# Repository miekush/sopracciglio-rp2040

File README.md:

# Sopracciglio RP2040
Raspberry Pi RP2040 based Sopracciglio Board for use with 2026 Open Sauce Badge

# Schematic

# Layout

# Installation

1. Clone repo to a folder of your choice
2. Open the project in KiCad V10.99
3. "Save As" with the name of your project
4. Enjoy! :)

# License

miekush supports the open source hardware community by sharing hardware design files freely on GitHub!

Designed by Mike Kushnerik (miekush)

Licensed under [Creative Commons Attribution-ShareAlike CC BY-SA 4.0](http://creativecommons.org/licenses/by-sa/4.0/)

All text above must be included in any redistribution!

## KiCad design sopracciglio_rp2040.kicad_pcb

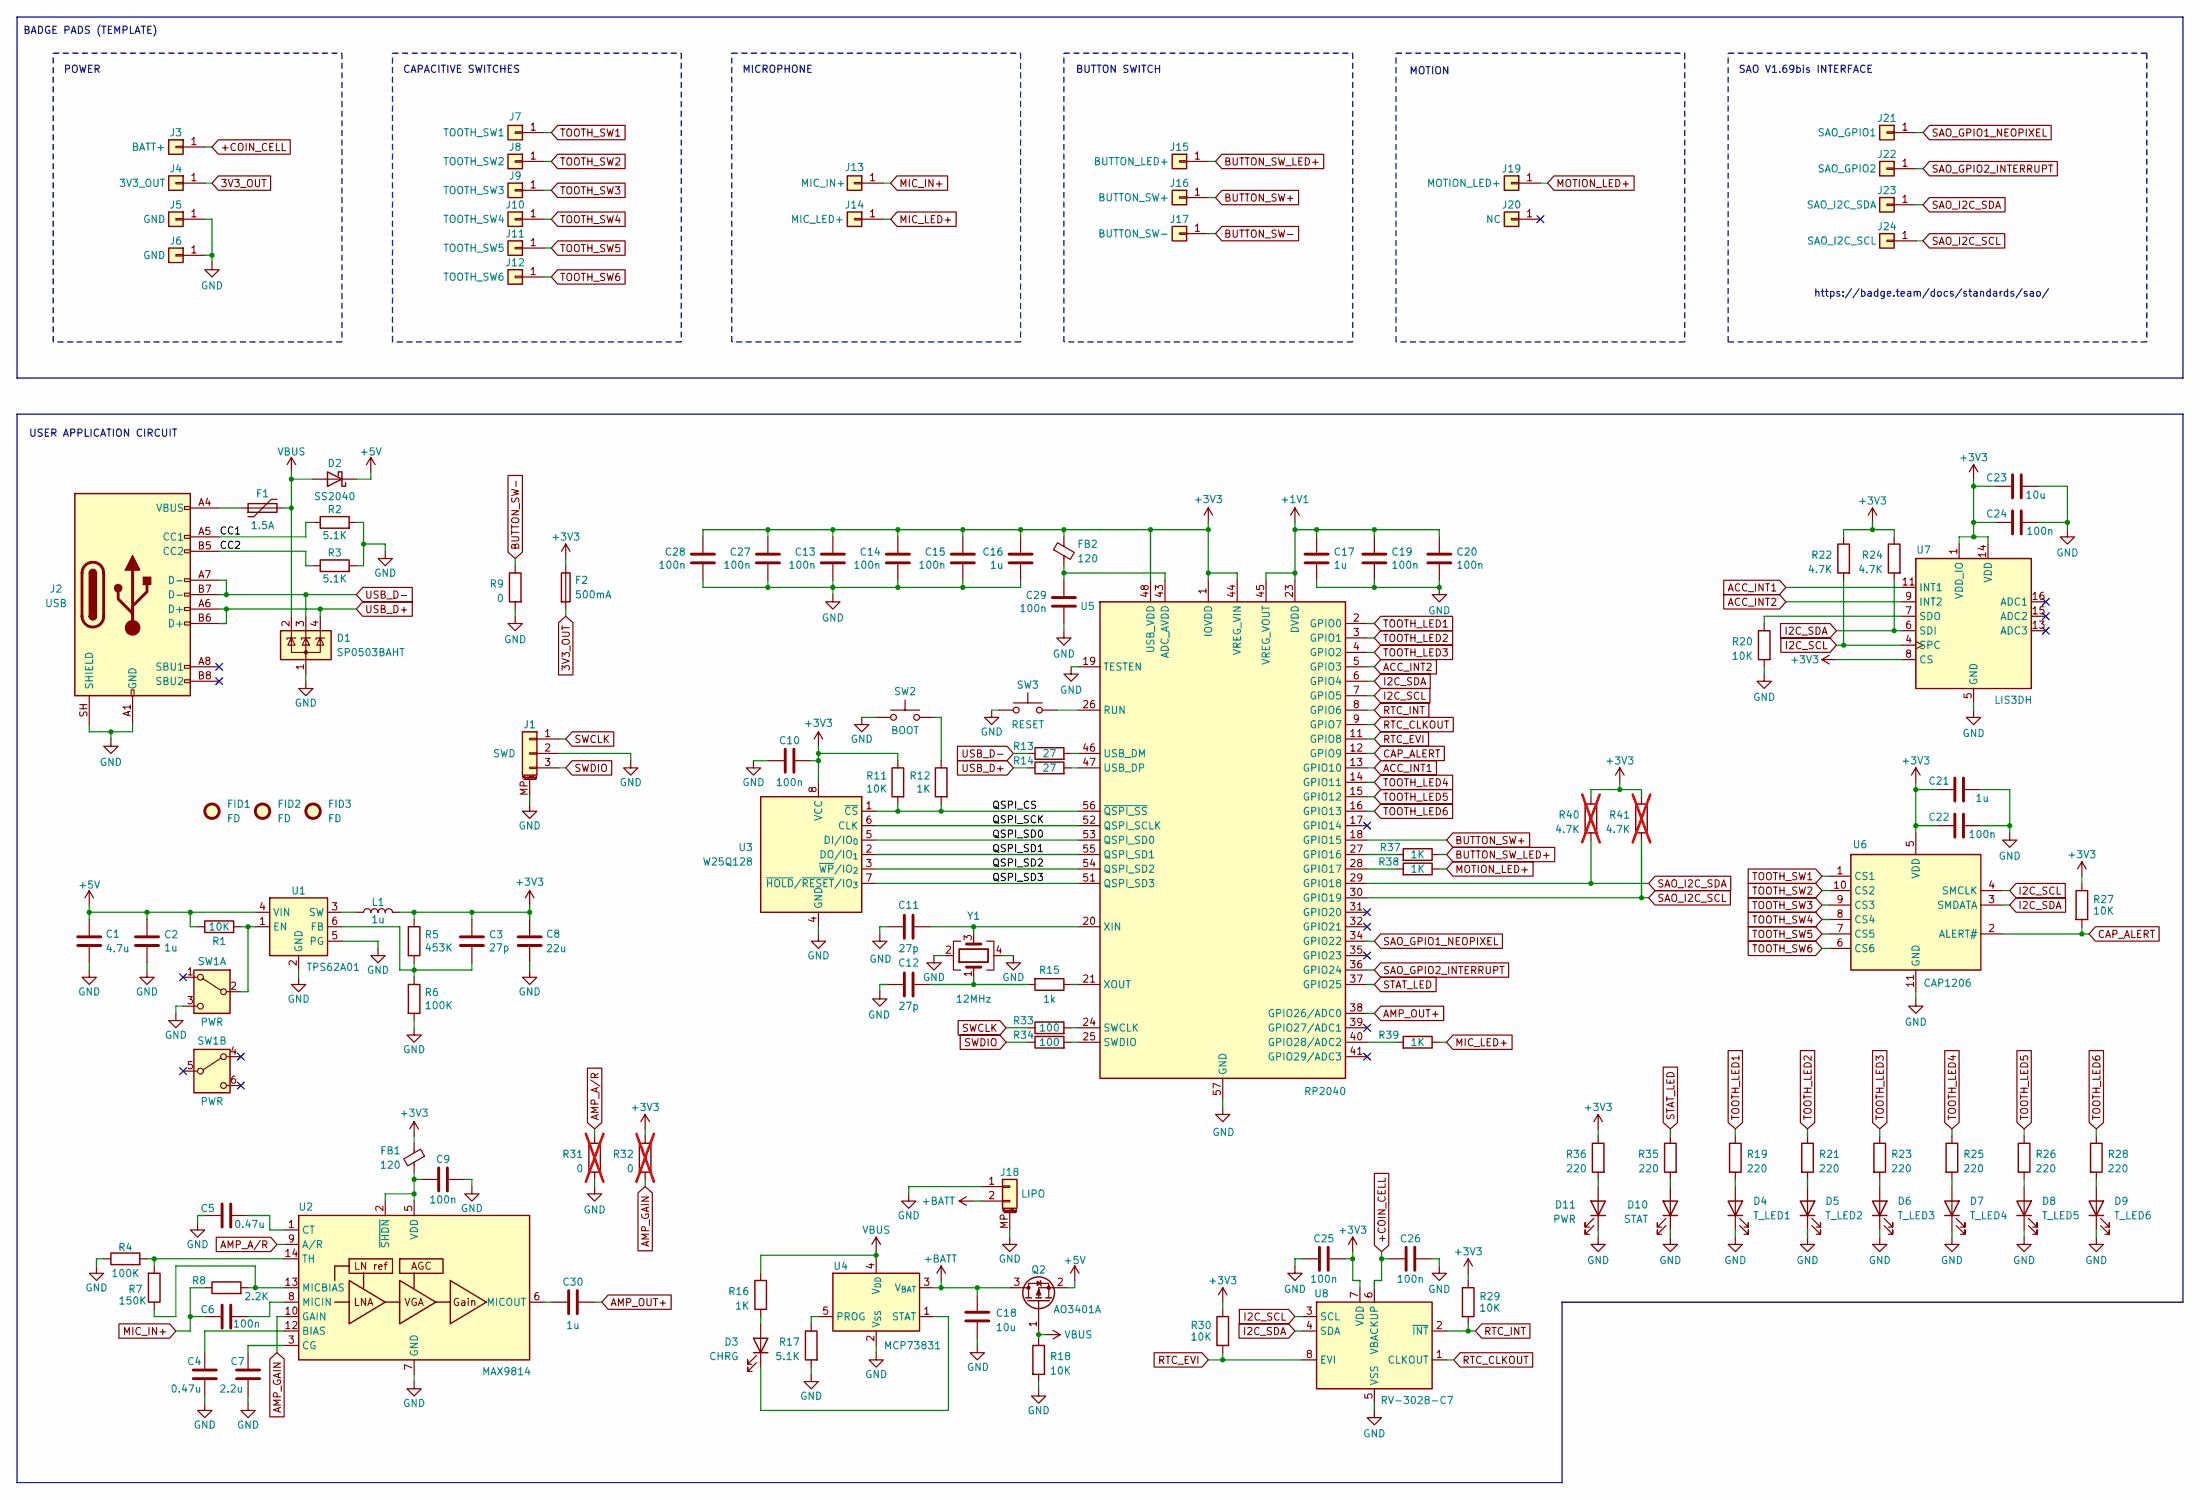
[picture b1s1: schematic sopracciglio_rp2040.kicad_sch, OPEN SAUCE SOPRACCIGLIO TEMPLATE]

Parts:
C1: 4.7u; C_0805_2012Metric
C2, C16, C17, C21, C30: 1u; C_0603_1608Metric
C3, C11, C12: 27p; C_0402_1005Metric
C4, C5: 0.47u; C_0603_1608Metric
C6, C9, C10, C13, C14, C15, C19, C20, C22, C24, C25, C26, C27, C28, C29: 100n; C_0402_1005Metric
C7: 2.2u; C_0603_1608Metric
C8: 22u; C_0805_2012Metric
C18, C23: 10u; C_0805_2012Metric
D1: SP0503BAHT; SOT-143
D2: SS2040; D_SOD-123F
D3: CHRG; LED_0603_1608Metric
D4: T_LED1; LED_0603_1608Metric
D5: T_LED2; LED_0603_1608Metric
D6: T_LED3; LED_0603_1608Metric
D7: T_LED4; LED_0603_1608Metric
D8: T_LED5; LED_0603_1608Metric
D9: T_LED6; LED_0603_1608Metric
D10: STAT; LED_0603_1608Metric
D11: PWR; LED_0603_1608Metric
F1: 1.5A; Fuse_1206_3216Metric
F2: 500mA; Fuse_0402_1005Metric
FB1, FB2: 120; L_0402_1005Metric
FID1, FID2, FID3: FD; Fiducial_0.75mm_Mask1.5mm
J1: SWD; JST_SH_SM03B-SRSS-TB_1x03-1MP_P1.00mm_Horizontal
J2: USB; USB_C_Receptacle_GCT_USB4110
J3: BATT+; castellated_pad
J4: 3V3_OUT; castellated_pad
J5, J6: GND; castellated_pad
J7: TOOTH_SW1; castellated_pad
J8: TOOTH_SW2; castellated_pad
J9: TOOTH_SW3; castellated_pad
J10: TOOTH_SW4; castellated_pad
J11: TOOTH_SW5; castellated_pad
J12: TOOTH_SW6; castellated_pad
J13: MIC_IN+; castellated_pad
J14: MIC_LED+; castellated_pad
J15: BUTTON_LED+; castellated_pad
J16: BUTTON_SW+; castellated_pad
J17: BUTTON_SW-; castellated_pad
J18: LIPO; JST_PH_S2B-PH-SM4-TB_1x02-1MP_P2.00mm_Horizontal
J19: MOTION_LED+; castellated_pad
J20: NC; castellated_pad
J21: SAO_GPIO1; castellated_pad
J22: SAO_GPIO2; castellated_pad
J23: SAO_I2C_SDA; castellated_pad
J24: SAO_I2C_SCL; castellated_pad
L1: 1u; L_1008_2520Metric
Q2: AO3401A; SOT-23
R1, R11, R18, R20, R27, R29, R30: 10K; R_0402_1005Metric
R2, R3, R17: 5.1K; R_0402_1005Metric
R4, R6: 100K; R_0402_1005Metric
R5: 453K; R_0402_1005Metric
R7: 150K; R_0402_1005Metric
R8: 2.2K; R_0402_1005Metric
R9: 0; R_0402_1005Metric
R12, R16, R37, R38, R39: 1K; R_0402_1005Metric
R13, R14: 27; R_0402_1005Metric
R15: 1k; R_0402_1005Metric
R19, R21, R23, R25, R26, R28, R35, R36: 220; R_0402_1005Metric
R22, R24: 4.7K; R_0402_1005Metric
R31, R32: 0; R_0402_1005Metric; not fitted
R33, R34: 100; R_0402_1005Metric
R40, R41: 4.7K; R_0402_1005Metric; not fitted
SW1: PWR; SW_DPDT_CK_JS202011JCQN
SW2: BOOT; SW_Push_1P1T_NO_CK_KMR2
SW3: RESET; SW_Push_1P1T_NO_CK_KMR2
U1: TPS62A01; SOT-23-6
U2: MAX9814; DFN-14-1EP_3x3mm_P0.4mm_EP1.78x2.35mm
U3: W25Q128; SOIC-8_5.3x5.3mm_P1.27mm
U4: MCP73831; SOT-23-5
U5: RP2040; QFN-56-1EP_7x7mm_P0.4mm_EP3.2x3.2mm
U6: CAP1206; DFN-10-1EP_3x3mm_P0.5mm_EP1.55x2.48mm
U7: LIS3DH; LGA-16_3x3mm_P0.5mm_LayoutBorder3x5y
U8: RV-3028-C7; MicroCrystal_C7_SON-8_1.5x3.2mm_P0.9mm
Y1: 12MHz; Crystal_SMD_Abracon_ABM8G-4Pin_3.2x2.5mm

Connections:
3V3_OUT: F2.2, J4.1 (Pin_1_1)
+1V1: C17.1, C19.1, C20.1, U5.23 (DVDD), U5.45 (VREG_VOUT), U5.50 (DVDD)
+3V3: C3.1, C8.1, C10.1, C13.1, C14.1, C15.1, C16.1, C21.1, C22.1, C23.1, C24.1, C25.1, C27.1, C28.1, F2.1, FB1.1, FB2.1, L1.2, R5.1, R11.1, R22.1, R24.1, R27.1, R29.1, R30.1, R32.1, R36.1, R40.1, R41.1, U3.8 (VCC), U5.1 (IOVDD), U5.10 (IOVDD), U5.22 (IOVDD), U5.33 (IOVDD), U5.42 (IOVDD), U5.44 (VREG_VIN), U5.48 (USB_VDD), U5.49 (IOVDD), U6.5 (VDD), U7.1 (VDD_IO), U7.8 (CS), U7.14 (VDD), U8.7 (VDD)
+5V: C1.1, C2.1, D2.1 (K), Q2.2 (S), R1.1, U1.4 (VIN)
+BATT: C18.1, J18.2, Q2.3 (D), U4.3 (V_{BAT})
+COIN_CELL: C26.1, J3.1 (Pin_1_1), U8.6 (VBACKUP)
/CC1: J2.A5 (CC1), R2.1
/CC2: J2.B5 (CC2), R3.1
/QSPI_CS: R11.2, R12.2, U3.1 (~CS), U5.56 (~QSPI_SS)
/QSPI_SCK: U3.6 (CLK), U5.52 (QSPI_SCLK)
/QSPI_SD0: U3.5 (DI/IO_{0}), U5.53 (QSPI_SD0)
/QSPI_SD1: U3.2 (DO/IO_{1}), U5.55 (QSPI_SD1)
/QSPI_SD2: U3.3 (~WP/IO_{2}), U5.54 (QSPI_SD2)
/QSPI_SD3: U3.7 (~HOLD/~RESET/IO_{3}), U5.51 (QSPI_SD3)
ACC_INT1: U5.13 (GPIO10), U7.11 (INT1)
ACC_INT2: U5.5 (GPIO3), U7.9 (INT2)
AMP_A/R: R31.1, U2.9 (A/R)
AMP_GAIN: R32.2, U2.10 (GAIN)
AMP_OUT+: C30.2, U5.38 (GPIO26/ADC0)
BUTTON_SW+: J16.1 (Pin_1_1), U5.18 (GPIO15)
BUTTON_SW-: J17.1 (Pin_1_1), R9.1
BUTTON_SW_LED+: J15.1 (Pin_1_1), R37.1
CAP_ALERT: R27.2, U5.12 (GPIO9), U6.2 (ALERT#)
GND: C1.2, C2.2, C4.1, C5.1, C7.1, C8.2, C9.2, C10.2, C11.2, C12.2, C13.2, C14.2, C15.2, C16.2, C17.2, C18.2, C19.2, C20.2, C21.2, C22.2, C23.2, C24.2, C25.2, C26.2, C27.2, C28.2, C29.2, D1.1 (A), D4.1 (K), D5.1 (K), D6.1 (K), D7.1 (K), D8.1 (K), D9.1 (K), D10.1 (K), D11.1 (K), J1.2, J1.MP (MountPin), J2.A1 (GND), J2.A12 (GND), J2.B1 (GND), J2.B12 (GND), J2.SH (SHIELD), J5.1 (Pin_1_1), J6.1 (Pin_1_1), J18.1, J18.MP (MountPin), R2.2, R3.2, R4.1, R6.2, R9.2, R17.2, R18.2, R20.2, R31.2, SW1.3 (C), SW2.2, SW3.1, U1.2 (GND), U1.5 (PG), U2.4 (GND), U2.7 (GND), U2.11 (GND), U2.15 (GND), U3.4 (GND), U4.2 (V_{SS}), U5.19 (TESTEN), U5.57 (GND), U6.11 (GND), U7.5 (GND), U7.10 (GND), U7.12 (GND), U8.5 (VSS), Y1.2, Y1.4
I2C_SCL: R22.2, U5.7 (GPIO5), U6.4 (SMCLK), U7.4 (SPC), U8.3 (SCL)
I2C_SDA: R24.2, U5.6 (GPIO4), U6.3 (SMDATA), U7.6 (SDI), U8.4 (SDA)
MIC_IN+: C6.1, J13.1 (Pin_1_1), R8.1
MIC_LED+: J14.1 (Pin_1_1), R39.1
MOTION_LED+: J19.1 (Pin_1_1), R38.1
unnamed: C12.1, R15.2, Y1.1
unnamed: D3.2 (A), R16.2
unnamed: D3.1 (K), U4.1 (STAT)
unnamed: D4.2 (A), R19.2
unnamed: D5.2 (A), R21.2
unnamed: D6.2 (A), R23.2
unnamed: D7.2 (A), R25.2
unnamed: D8.2 (A), R26.2
unnamed: D9.2 (A), R28.2
unnamed: D10.2 (A), R35.2
unnamed: D11.2 (A), R36.2
unnamed: F1.1, J2.A4 (VBUS), J2.A9 (VBUS), J2.B4 (VBUS), J2.B9 (VBUS)
unnamed: R12.1, SW2.1
unnamed: R1.2, SW1.2 (B), U1.1 (EN)
unnamed: C3.2, R5.2, R6.1, U1.6 (FB)
unnamed: L1.1, U1.3 (SW)
unnamed: C4.2, U2.12 (BIAS)
unnamed: C7.2, U2.3 (CG)
unnamed: C5.2, U2.1 (CT)
unnamed: R7.1, R8.2, U2.13 (MICBIAS)
unnamed: C6.2, U2.8 (MICIN)
unnamed: C30.1, U2.6 (MICOUT)
unnamed: R4.2, R7.2, U2.14 (TH)
unnamed: C9.1, FB1.2, U2.2 (~SHDN), U2.5 (VDD)
unnamed: R17.1, U4.5 (PROG)
unnamed: C29.1, FB2.2, U5.43 (ADC_AVDD)
unnamed: R37.2, U5.27 (GPIO16)
unnamed: R38.2, U5.28 (GPIO17)
unnamed: R39.2, U5.40 (GPIO28/ADC2)
unnamed: SW3.2, U5.26 (RUN)
unnamed: R33.2, U5.24 (SWCLK)
unnamed: R34.2, U5.25 (SWDIO)
unnamed: R13.2, U5.46 (USB_DM)
unnamed: R14.2, U5.47 (USB_DP)
unnamed: C11.1, U5.20 (XIN), Y1.3
unnamed: R15.1, U5.21 (XOUT)
unnamed: R20.1, U7.7 (SDO)
RTC_CLKOUT: U5.9 (GPIO7), U8.1 (CLKOUT)
RTC_EVI: R30.2, U5.11 (GPIO8), U8.8 (EVI)
RTC_INT: R29.2, U5.8 (GPIO6), U8.2 (~INT)
SAO_GPIO1_NEOPIXEL: J21.1 (Pin_1_1), U5.34 (GPIO22)
SAO_GPIO2_INTERRUPT: J22.1 (Pin_1_1), U5.36 (GPIO24)
SAO_I2C_SCL: J24.1 (Pin_1_1), R41.2, U5.30 (GPIO19)
SAO_I2C_SDA: J23.1 (Pin_1_1), R40.2, U5.29 (GPIO18)
STAT_LED: R35.1, U5.37 (GPIO25)
SWCLK: J1.1, R33.1
SWDIO: J1.3, R34.1
TOOTH_LED1: R19.1, U5.2 (GPIO0)
TOOTH_LED2: R21.1, U5.3 (GPIO1)
TOOTH_LED3: R23.1, U5.4 (GPIO2)
TOOTH_LED4: R25.1, U5.14 (GPIO11)
TOOTH_LED5: R26.1, U5.15 (GPIO12)
TOOTH_LED6: R28.1, U5.16 (GPIO13)
TOOTH_SW1: J7.1 (Pin_1_1), U6.1 (CS1)
TOOTH_SW2: J8.1 (Pin_1_1), U6.10 (CS2)
TOOTH_SW3: J9.1 (Pin_1_1), U6.9 (CS3)
TOOTH_SW4: J10.1 (Pin_1_1), U6.8 (CS4)
TOOTH_SW5: J11.1 (Pin_1_1), U6.7 (CS5)
TOOTH_SW6: J12.1 (Pin_1_1), U6.6 (CS6)
USB_D+: D1.4 (K), J2.A6 (D+), J2.B6 (D+), R14.1
USB_D-: D1.3 (K), J2.A7 (D-), J2.B7 (D-), R13.1
VBUS: D1.2 (K), D2.2 (A), F1.2, Q2.1 (G), R16.1, R18.1, U4.4 (V_{DD})

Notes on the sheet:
SAO V1.69bis INTERFACE
https://badge.team/docs/standards/sao/
CAPACITIVE SWITCHES
BUTTON SWITCH
POWER
USER APPLICATION CIRCUIT
MOTION
MICROPHONE
BADGE PADS (TEMPLATE)

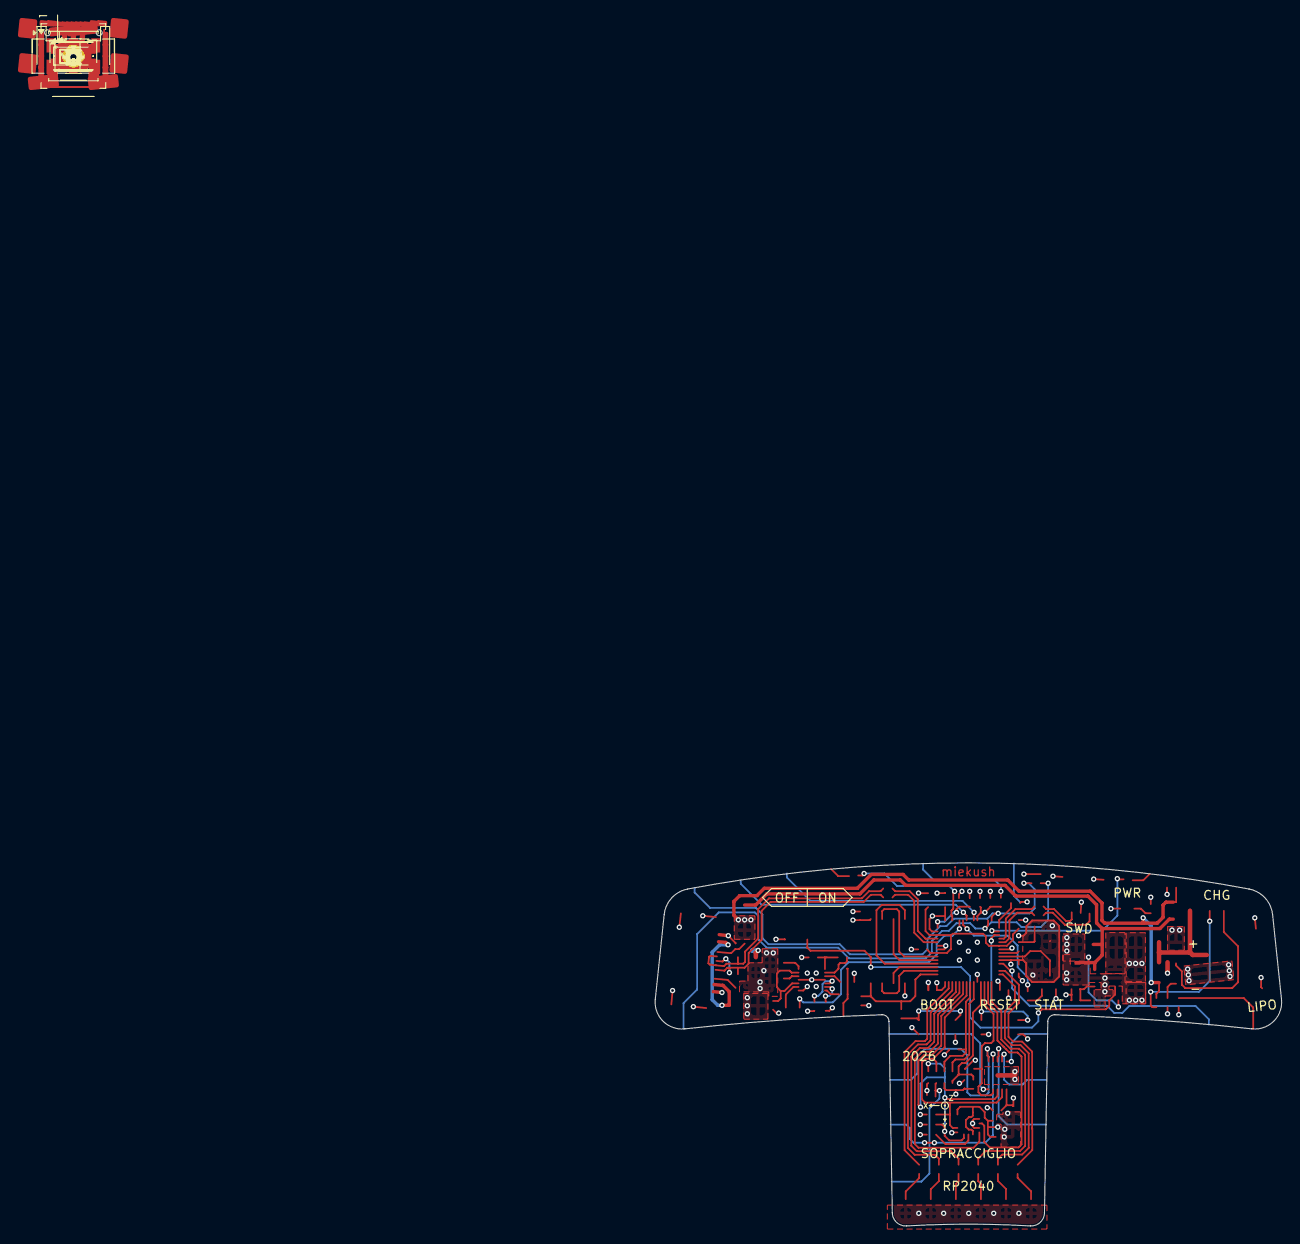
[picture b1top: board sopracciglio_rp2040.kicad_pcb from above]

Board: 4 copper layers, 70.0 x 40.6 mm, 126 parts (0 on the bottom side), 91 nets.

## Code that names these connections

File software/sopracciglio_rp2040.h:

//sopracciglio_rp2040.h
//author: mike kushnerik
//date: 9/25/2026

#ifndef _SOPRACCIGLIO_RP2040_H_
#define _SOPRACCIGLIO_RP2040_H_

#include <Arduino.h>

#ifdef __cplusplus
extern "C" {
#endif

//onboard i2c bus for rtc, cap touch controller, and accelerometer
#define I2C0_SDA        4
#define I2C0_SCL        5

//i2c addresses
#define CAP1206_ADDR    0x28
#define LIS3DH_ADDR     0x30
#define RV3028_ADDR     0x52

//cap1206 registers
#define CAP1206_MAIN_CONTROL          0x00
#define CAP1206_GENERAL_STATUS        0x02
#define CAP1206_SENSOR_INPUT_STATUS   0x03

//tooth leds
#define T_LED_1         0
#define T_LED_2         1
#define T_LED_3         2
#define T_LED_4         11
#define T_LED_5         12
#define T_LED_6         13

//accelerometer pins
#define ACC_INT1        10
#define ACC_INT2        3

//rtc pins
#define RTC_INT         6
#define RTC_CLKOUT      7
#define RTC_EVI         8

//cap touch pins
#define CAP_ALERT       9

//sao pins
#define SAO_GPIO1       22
#define SAO_GPIO2       24
#define SAO_I2C_SDA     18
#define SAO_I2C_SCL     19

//onboard leds
#define STAT_LED        25

//microphone
#define MIC_AUDIO_IN    26

/// badge i/o ///

//button switch
#define BUTTON_SW       15
#define BUTTON_SW_LED   16

//motion
#define MOTION_LED      17

//microphone
#define MIC_LED         28

//function prototypes
void sopracciglio_rp2040_init(void);

#ifdef __cplusplus
}
#endif

#endif
